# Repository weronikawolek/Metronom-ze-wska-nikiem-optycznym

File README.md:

# Metronom-ze-wska-nikiem-optycznym
Projekt płytki PCB na podstawie udostępnionego wzoru.

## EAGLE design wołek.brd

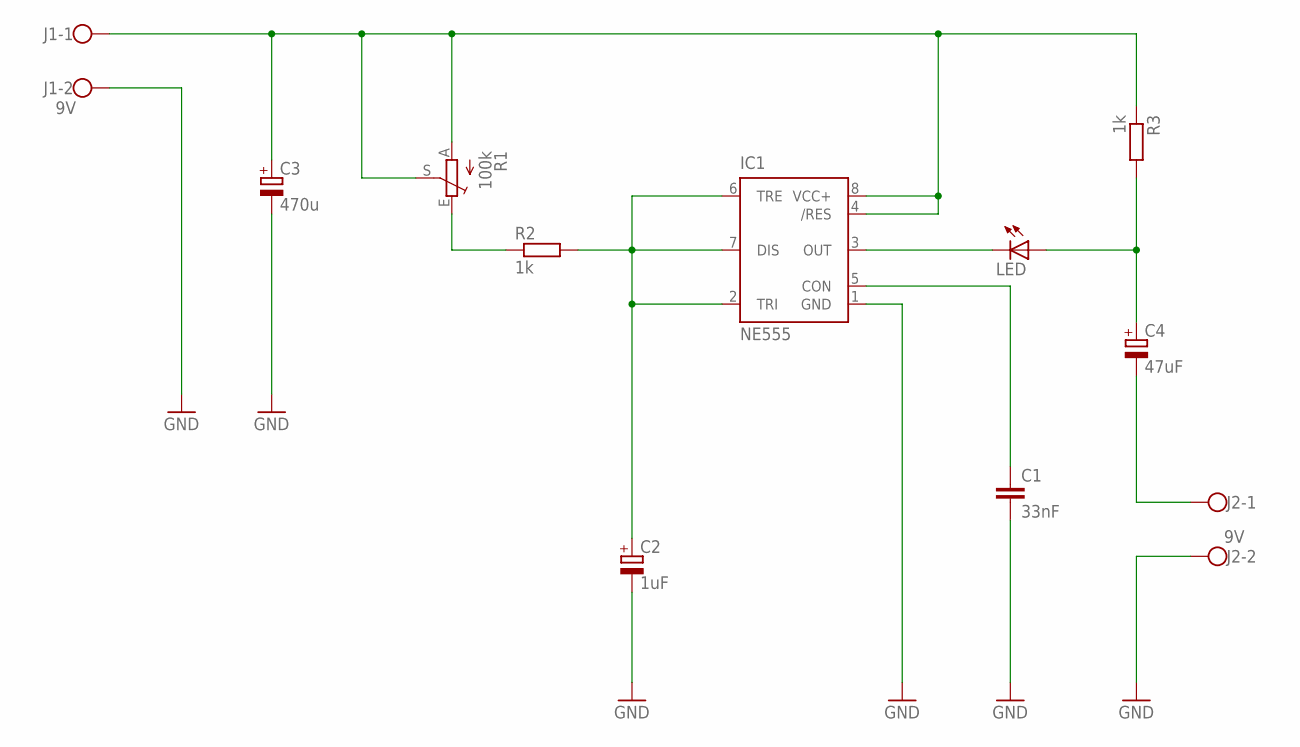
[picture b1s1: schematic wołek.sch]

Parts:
C1: 33nF; C1206K
C2: 1uF; E5-8,5
C3: 470u; E7,5-16
C4: 47uF; E5-8,5
IC1: NE555; DIL-08
J1, J2: 9V; W237-102
LED: LED_LED3MM
R1: 100k; CA6V
R2, R3: 1k; R1210W

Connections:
GND: C1.2, C2.-, C3.-, IC1.1 (GND), J1.2, J2.2
unnamed: C3.+, IC1.4 (/RES), IC1.8 (VCC+), J1.1, R1.A, R1.S, R3.1
unnamed: C4.+, LED.A, R3.2
unnamed: C4.-, J2.1
unnamed: C2.+, IC1.2 (TRI), IC1.6 (TRE), IC1.7 (DIS), R2.2
unnamed: IC1.3 (OUT), LED.K (C)
unnamed: R1.E, R2.1
unnamed: C1.1, IC1.5 (CON)

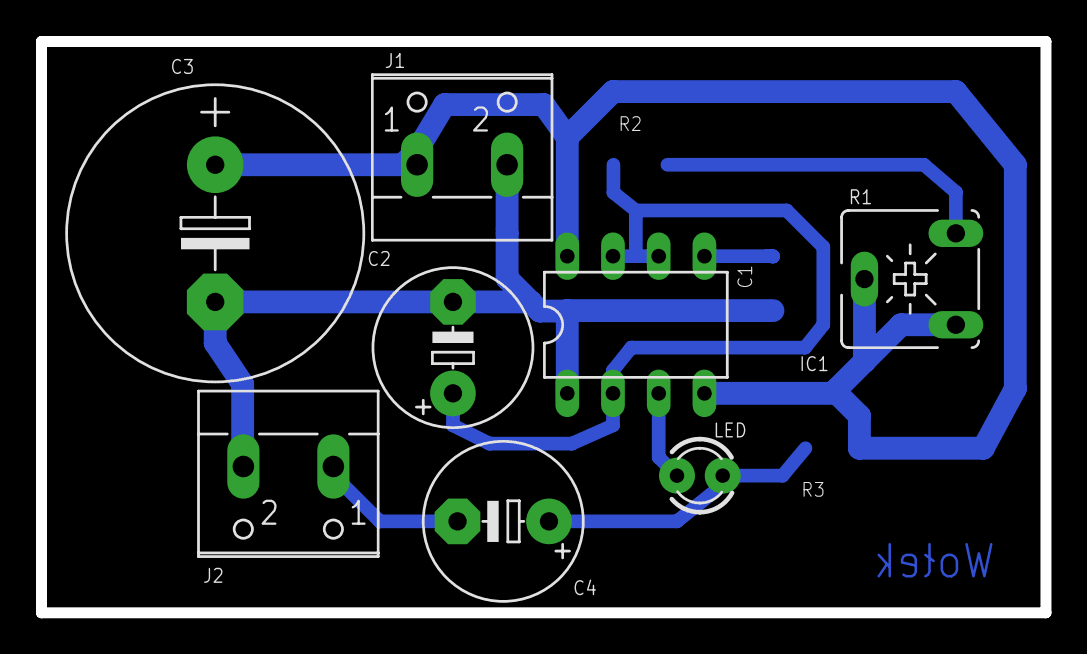
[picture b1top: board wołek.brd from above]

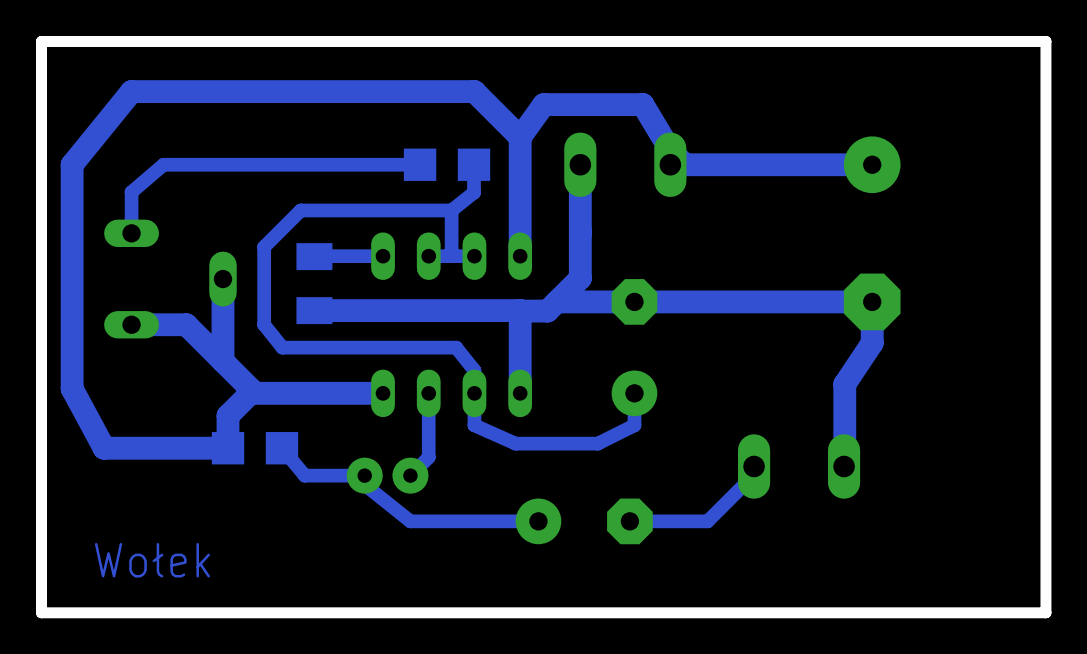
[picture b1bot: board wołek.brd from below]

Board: 2 copper layers, 55.8 x 31.7 mm, 11 parts (3 on the bottom side), 8 nets.
